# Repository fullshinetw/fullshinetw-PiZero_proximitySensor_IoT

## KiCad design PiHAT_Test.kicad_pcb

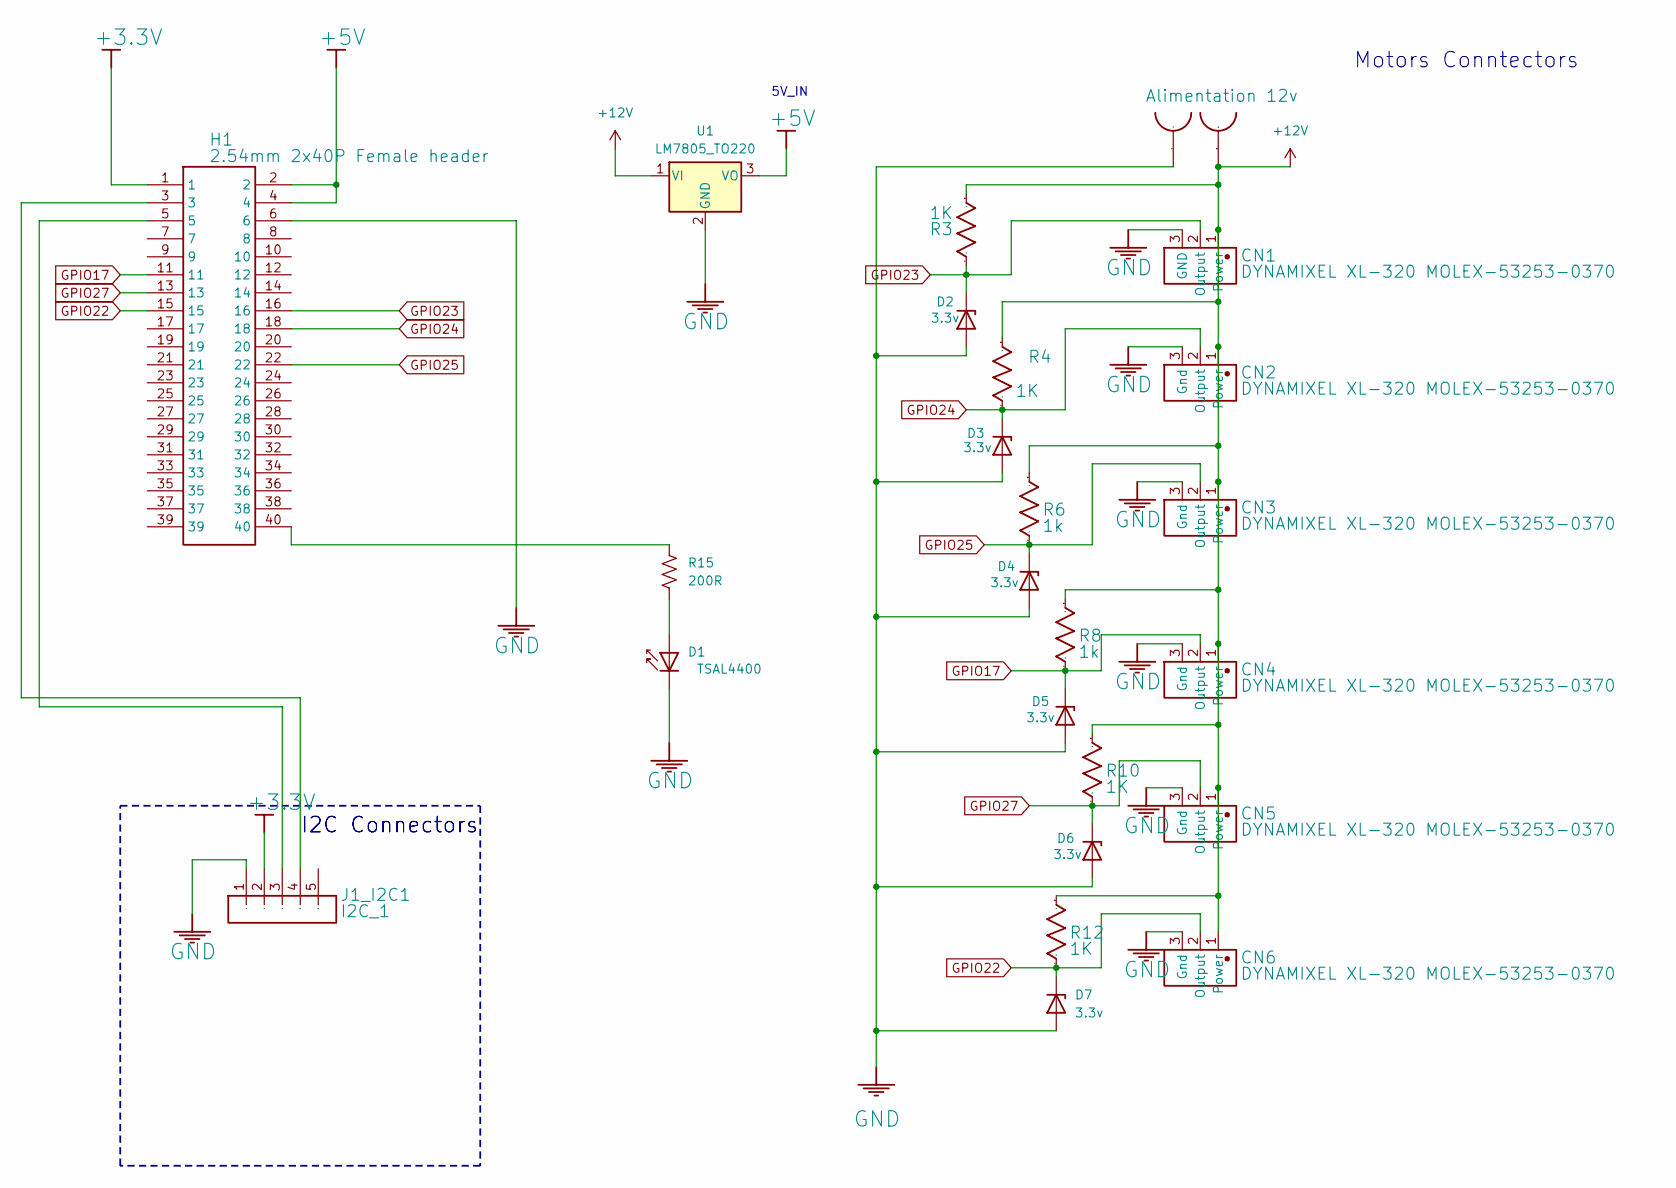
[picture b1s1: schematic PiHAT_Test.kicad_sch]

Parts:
CN1, CN2, CN3, CN4, CN5, CN6: DYNAMIXEL XL-320 MOLEX-53253-0370; PinHeader_1x03_P2.54mm_Horizontal
D1: TSAL4400; LED_D3.0mm_IRBlack
D2, D3, D4, D5, D6, D7: 3.3v; D_DO-41_SOD81_P2.54mm_Vertical_AnodeUp
H1: 2.54mm 2x40P Female header; Raspberry_Pi_Zero_Socketed_THT_FaceDown_MountingHoles; Manufacturer Part 2.54mm 2x40P Female header
J1_I2C1: I2C_1; PinHeader_1x05_P2.54mm_Vertical
R3, R4, R10, R12: 1K; R_Axial_DIN0204_L3.6mm_D1.6mm_P2.54mm_Vertical
R6, R8: 1k; R_Axial_DIN0204_L3.6mm_D1.6mm_P2.54mm_Vertical
R15: 200R; R_Axial_DIN0204_L3.6mm_D1.6mm_P2.54mm_Vertical
U1: LM7805_TO220; TO-220-3_Vertical
U2: Alimentation 12v; PhoenixContact_MCV_1,5_2-G-3.81_1x02_P3.81mm_Vertical

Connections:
+3.3V: H1.1, J1_I2C1.2
+5V: H1.2, H1.4, U1.3 (VO)
+12V: CN1.1 (Power), CN2.1 (Power), CN3.1 (Power), CN4.1 (Power), CN5.1 (Power), CN6.1 (Power), R3.1, R4.1, R6.1, R8.1, R10.1, R12.1, U1.1 (VI), U2.1
GND: CN1.3 (GND), CN2.3 (Gnd), CN3.3 (Gnd), CN4.3 (Gnd), CN5.3 (Gnd), CN6.3 (Gnd), D1.1 (K), D2.2 (A), D3.2 (A), D4.2 (A), D5.2 (A), D6.2 (A), D7.2 (A), H1.6, J1_I2C1.1, U1.2 (GND), U2.2
GPIO17: CN4.2 (Output), D5.1 (K), H1.11, R8.2
GPIO22: CN6.2 (Output), D7.1 (K), H1.15, R12.2
GPIO23: CN1.2 (Output), D2.1 (K), H1.16, R3.2
GPIO24: CN2.2 (Output), D3.1 (K), H1.18, R4.2
GPIO25: CN3.2 (Output), D4.1 (K), H1.22, R6.2
GPIO27: CN5.2 (Output), D6.1 (K), H1.13, R10.2
unnamed: D1.2 (A), R15.2
unnamed: H1.3, J1_I2C1.4
unnamed: H1.5, J1_I2C1.3
unnamed: H1.40, R15.1

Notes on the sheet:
5V_IN
Motors Conntectors
I2C Connectors

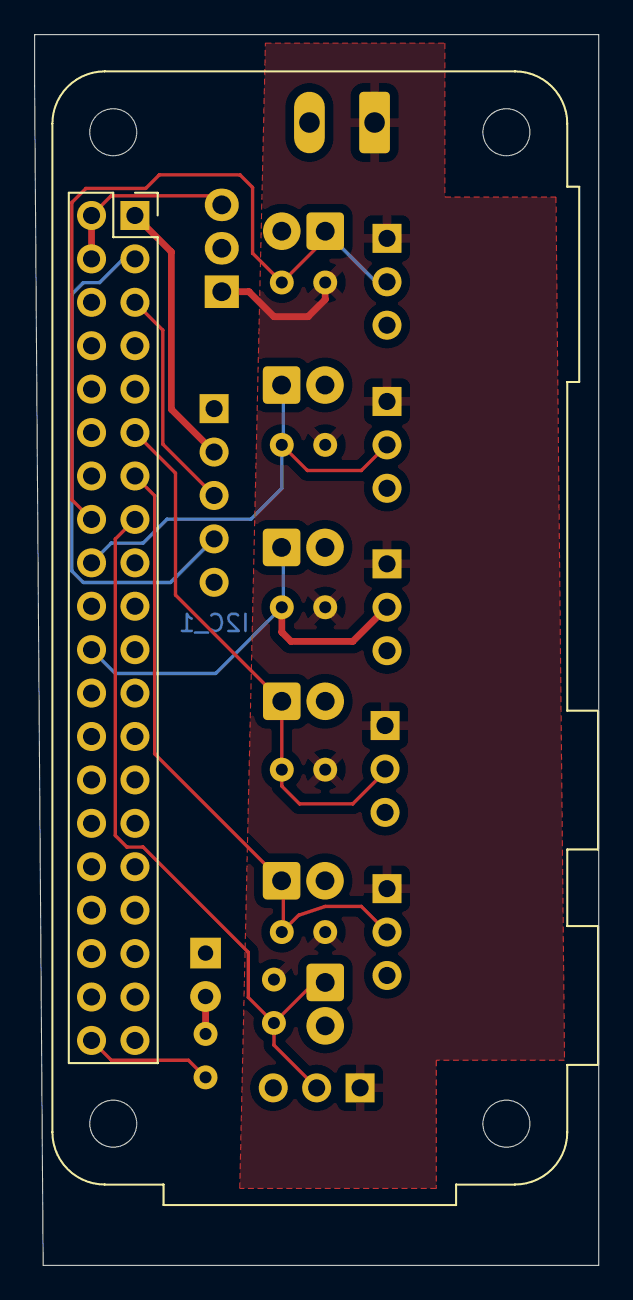
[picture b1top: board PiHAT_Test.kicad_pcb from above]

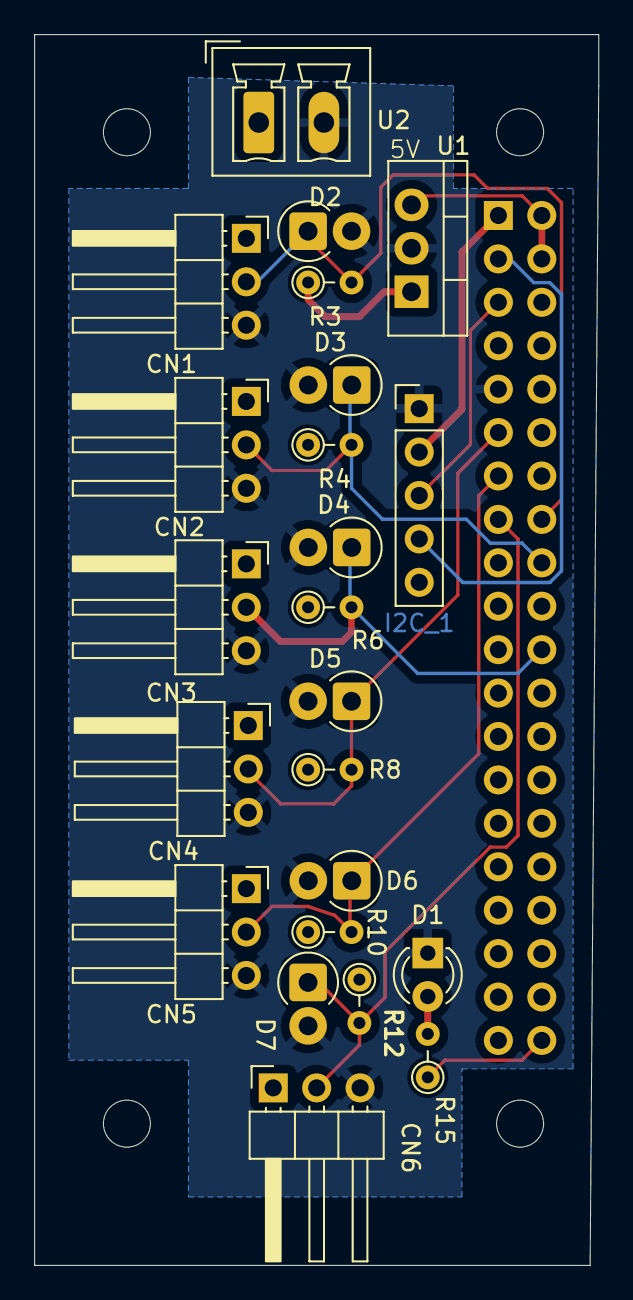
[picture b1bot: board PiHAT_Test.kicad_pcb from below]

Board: 2 copper layers, 33.0 x 72.0 mm, 24 parts (23 on the bottom side), 14 nets.

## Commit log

2025-07-13 Version 1.0
2025-07-16 Add 12V+ power and Gerber files
2025-07-16 Add 3D PCB view
2025-07-16 Update the final Gerber files to PCBWay and pay order
2025-07-26 Correct 5V regulator 12V input
2025-08-07 Add sensor_detection_csv.py script
2025-08-10 Add threading job in sensor_detection_csv.py script
2025-08-10 Remove debug info in sensor_detection_csv.py script
2025-08-16 Add hostname info to output file of sensor_detection_csv.py script
